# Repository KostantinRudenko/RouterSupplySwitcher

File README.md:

## RouterSupplySwitcher
RouterSupplySwitcher is a device designed for automatic power source switching for a router.

The device ensures uninterrupted router operation by automatically selecting the available power source and providing a stable 12V output.

## Hardware components

### Power input/output
- Barrel Jack ×2 (input/output)
- USB-A (output)
- USB-C (input)

### Power conversion
- XL6009 DC-DC boost converter
- Potentiometer 10 kΩ (output voltage adjustment)

### Protection and power routing
- Schottky diode SS34
- General-purpose diodes ×2

### Passive components
- Resistor 330 Ω
- Capacitors:
  - 220 µF ×1
  - 100 µF ×1
  - 0.1 µF ×2

Detailed wiring and connections are provided in the electronic schematic (PDF).

## Operating principle

The device accepts power from Barrel Jack or USB-C inputs.
If external power is present, the router is powered directly from the input source while maintaining a regulated 12V output.

In case of input power loss, the power path automatically switches, ensuring uninterrupted router operation.
Input voltage may vary between 5V and 12V, while the output voltage is regulated to a fixed 12V using a DC-DC boost converter.

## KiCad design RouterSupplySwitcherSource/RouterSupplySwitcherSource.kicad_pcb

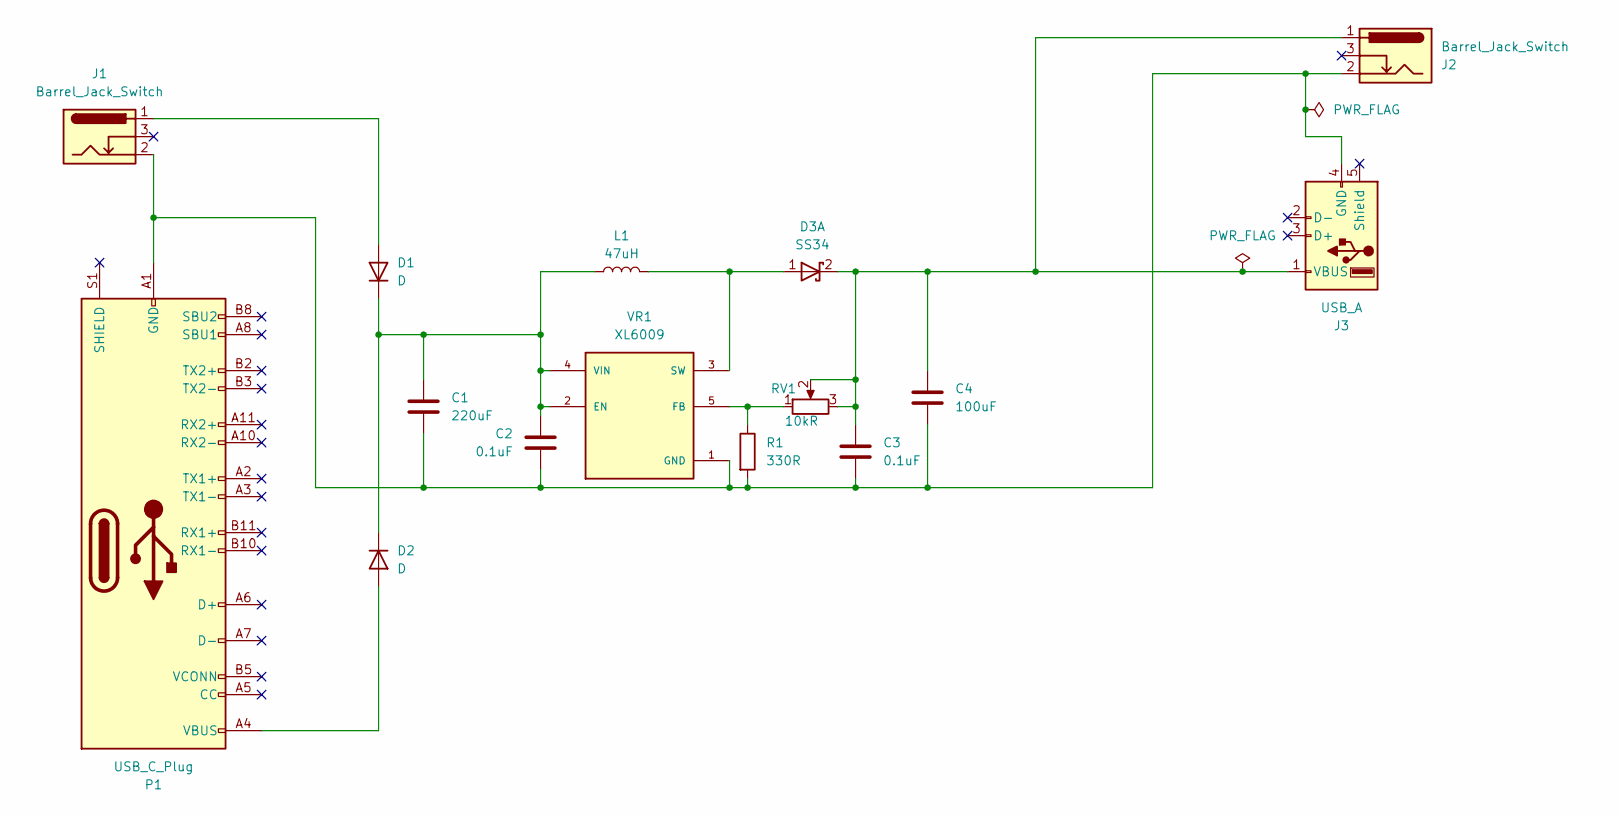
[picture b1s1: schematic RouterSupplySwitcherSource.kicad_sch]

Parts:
C1: 220uF; CP_Radial_D4.0mm_P2.00mm
C2, C3: 0.1uF; C_1210_3225Metric
C4: 100uF; CP_Radial_D4.0mm_P2.00mm
D1, D2: D; D_DO-15_P15.24mm_Horizontal
D3: SS34
J1, J2: Barrel_Jack_Switch; BarrelJack_GCT_DCJ200-10-A_Horizontal
J3: USB_A; USB_A_Receptacle_GCT_USB1046
L1: 47uH; L_10.4x10.4_H4.8
P1: USB_C_Plug; USB_C_Receptacle_GCT_USB4105-xx-A_16P_TopMnt_Horizontal
R1: 330R; R_Axial_DIN0207_L6.3mm_D2.5mm_P10.16mm_Horizontal
RV1: 10kR; Potentiometer_Bourns_3266Y_Vertical
VR1: XL6009; PARTREV 1.1

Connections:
unnamed: D1.2 (A), J1.1
unnamed: C1.1, C2.2, D1.1 (K), D2.1 (K), L1.1, VR1.2 (EN), VR1.4 (VIN)
unnamed: D2.2 (A), P1.A4 (VBUS), P1.A9 (VBUS), P1.B4 (VBUS), P1.B9 (VBUS)
unnamed: D3.1 (A), L1.2, VR1.3 (SW), VR1.6 (SW)
unnamed: C3.1, C4.1, D3.2 (K), J2.1, J3.1 (VBUS), RV1.2, RV1.3
unnamed: C1.2, C2.1, C3.2, C4.2, J1.2, J2.2, J3.4 (GND), P1.A1 (GND), P1.A12 (GND), P1.B1 (GND), P1.B12 (GND), R1.2, VR1.1 (GND)
unnamed: R1.1, RV1.1, VR1.5 (FB)

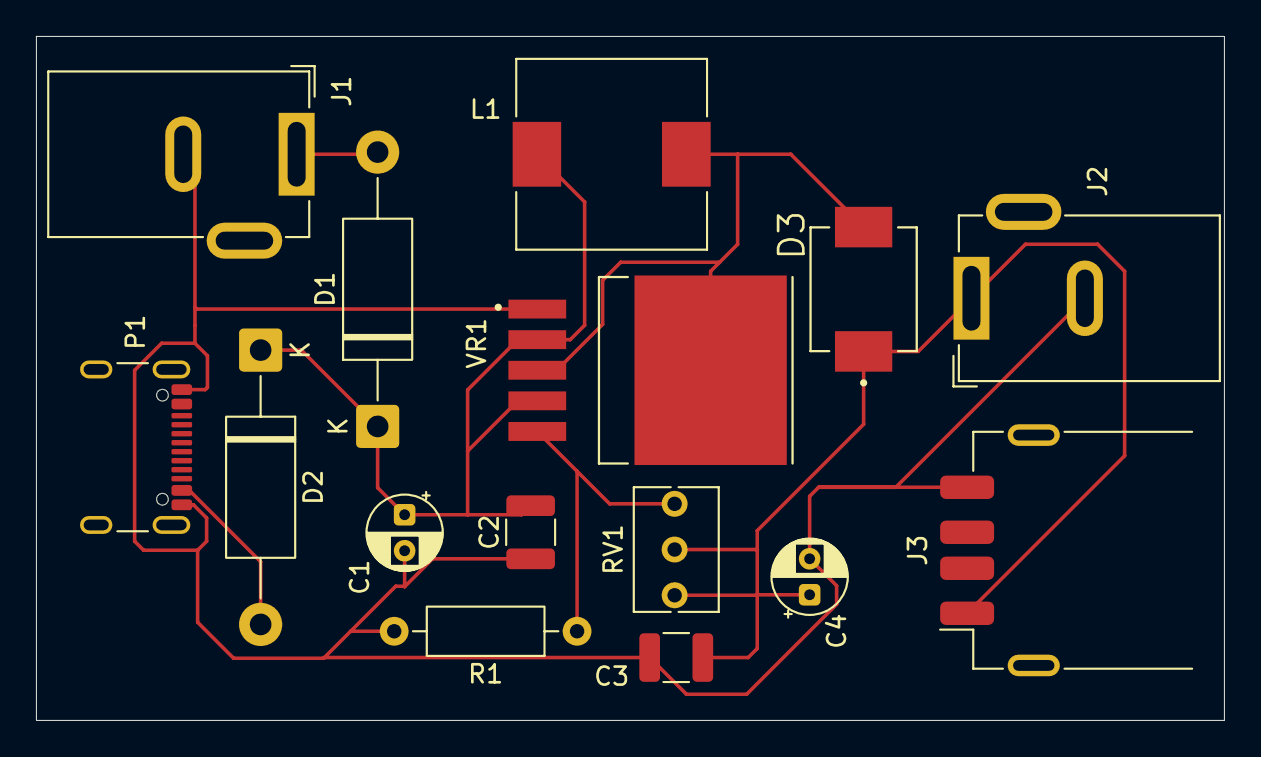
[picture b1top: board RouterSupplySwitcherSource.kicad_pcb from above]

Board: 2 copper layers, 66.0 x 38.0 mm, 15 parts (0 on the bottom side), 7 nets.

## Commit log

2025-12-28 added base files
2025-12-29 added scheme
2025-12-29 added gitignore
2025-12-29 some cache (I hz)
2025-12-30 added footprints
2026-01-02 added pcb
2026-01-02 added gerber
2026-01-02 added values
2026-01-02 added text
2026-01-02 added pdf
2026-01-02 Added README file
